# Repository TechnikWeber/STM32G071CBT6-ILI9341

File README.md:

# STM32G071 touch display board (ILI9341)

<p>

</p>

A custom STM32G071CBT6 board that carries an ILI9341 SPI TFT display on its back, with
demo firmware.

## What is on it

| Part | Purpose |
|---|---|
| STM32G071CBT6 | Cortex-M0+ MCU, 128 KB flash, 36 KB RAM |
| 16 MHz and 32.768 kHz crystals | Main clock and RTC |
| AMS1117-3.3 | 5 V → 3.3 V regulator |
| ILI9341 headers | The display module (SPI) |
| Tag-Connect TC2030 footprint (DEBUG) | SWD programming and debugging — see the [STDC14-to-TC2030 adapter](https://github.com/TechnikWeber/STDC14-to-TC2030-IDC) |
| 3-pin headers | UART (RX, TX, GND) and power (5 V, 3.3 V, GND) |
| RESET, BOOT0 and USER buttons, red LED | |

## Files

- `STM32G071.kicad_sch` / `.kicad_pcb` — schematic and PCB (KiCad)
- [`production/`](production) — Gerber/drill zip, BOM, positions and netlist
- [`Firmware/Display.7z`](Firmware) — STM32CubeIDE demo project for the display

## Known issue

> [!WARNING]
> **The ILI9341 footprint does not match** the display module that was bought
> ([AliExpress listing](https://de.aliexpress.com/item/32847628219.html)) — check the
> module's pin spacing and mounting holes before ordering boards.

## Pictures

## License

[MIT](LICENSE).

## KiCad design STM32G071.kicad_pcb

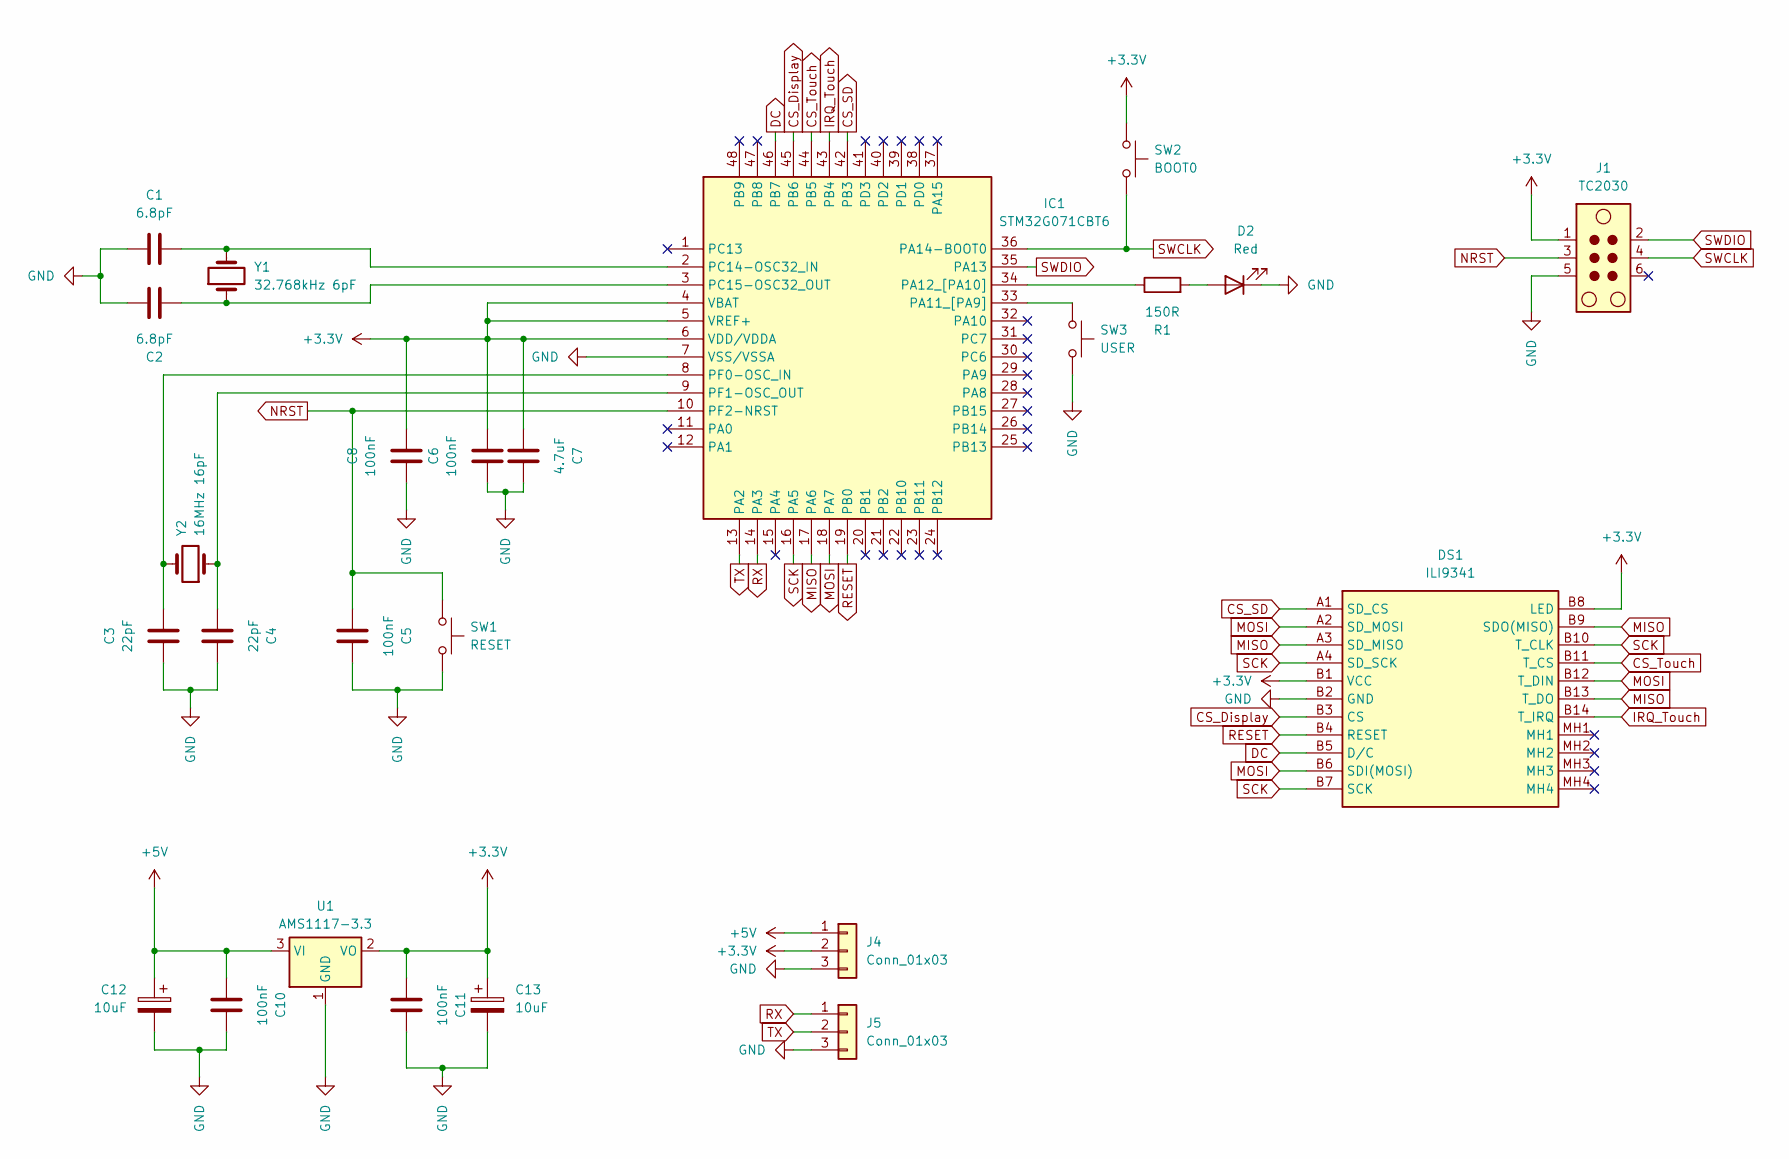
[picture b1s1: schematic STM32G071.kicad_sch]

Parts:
C1, C2: 6.8pF; C_0805_2012Metric; JLC C1832
C3: 22pF; C_0805_2012Metric; JLC C1804
C4: 22pF; C_0805_2012Metric
C5, C6, C8, C10, C11: 100nF; C_0805_2012Metric; JLC C49678
C7: 4.7uF; C_0805_2012Metric; JLC C1779
C12, C13: 10uF; CP_Radial_D6.3mm_P2.50mm
D2: Red; LED_0805_2012Metric
DS1: ILI9341; Manufacturer_Part_Number ILI9341
IC1: STM32G071CBT6; QFP50P900X900X160-48N; Manufacturer_Part_Number STM32G071CBT6; Mouser Part Number 511-STM32G071CBT6
J1: TC2030; Tag-Connect_TC2030-IDC-FP_2x03_P1.27mm_Vertical
J4, J5: Conn_01x03; PinHeader_1x03_P2.54mm_Vertical
R1: 150R; R_0805_2012Metric; JLC C17471
SW1: RESET; SW_SPST_PTS645Sx43SMTR92; JLC C7470157
SW2: BOOT0; SW_SPST_PTS645Sx43SMTR92; JLC C7470157
SW3: USER; SW_SPST_PTS645Sx43SMTR92; JLC C7470157
U1: AMS1117-3.3; SOT-223-3_TabPin2
Y1: 32.768kHz 6pF; Crystal_SMD_3215-2Pin_3.2x1.5mm; JLC C95361
Y2: 16MHz 16pF; Crystal_SMD_HC49-SD; JLC C19631568

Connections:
+3.3V: C6.2, C7.2, C8.2, C11.2, C13.1, DS1.B1 (VCC), DS1.B8 (LED), IC1.4 (VBAT), IC1.5 (VREF+), IC1.6 (VDD/VDDA), J1.1, J4.2, SW2.1, U1.2 (VO)
+5V: C10.2, C12.1, J4.1, U1.3 (VI)
CS_Display: DS1.B3 (CS), IC1.45 (PB6)
CS_SD: DS1.A1 (SD_CS), IC1.42 (PB3)
CS_Touch: DS1.B11 (T_CS), IC1.44 (PB5)
DC: DS1.B5 (D/C), IC1.46 (PB7)
GND: C1.1, C2.1, C3.1, C4.1, C5.1, C6.1, C7.1, C8.1, C10.1, C11.1, C12.2, C13.2, D2.1 (K), DS1.B2 (GND), IC1.7 (VSS/VSSA), J1.5, J4.3, J5.3, SW1.2, SW3.2, U1.1 (GND)
IRQ_Touch: DS1.B14 (T_IRQ), IC1.43 (PB4)
MISO: DS1.A3 (SD_MISO), DS1.B9 (SDO(MISO)), DS1.B13 (T_DO), IC1.17 (PA6)
MOSI: DS1.A2 (SD_MOSI), DS1.B6 (SDI(MOSI)), DS1.B12 (T_DIN), IC1.18 (PA7)
NRST: C5.2, IC1.10 (PF2-NRST), J1.3, SW1.1
unnamed: D2.2 (A), R1.2
unnamed: IC1.33 (PA11_[PA9]), SW3.1
unnamed: IC1.34 (PA12_[PA10]), R1.1
unnamed: C1.2, IC1.2 (PC14-OSC32_IN), Y1.2
unnamed: C2.2, IC1.3 (PC15-OSC32_OUT), Y1.1
unnamed: C3.2, IC1.8 (PF0-OSC_IN), Y2.2
unnamed: C4.2, IC1.9 (PF1-OSC_OUT), Y2.1
RESET: DS1.B4 (RESET), IC1.19 (PB0)
RX: IC1.14 (PA3), J5.1
SCK: DS1.A4 (SD_SCK), DS1.B7 (SCK), DS1.B10 (T_CLK), IC1.16 (PA5)
SWCLK: IC1.36 (PA14-BOOT0), J1.4, SW2.2
SWDIO: IC1.35 (PA13), J1.2
TX: IC1.13 (PA2), J5.2

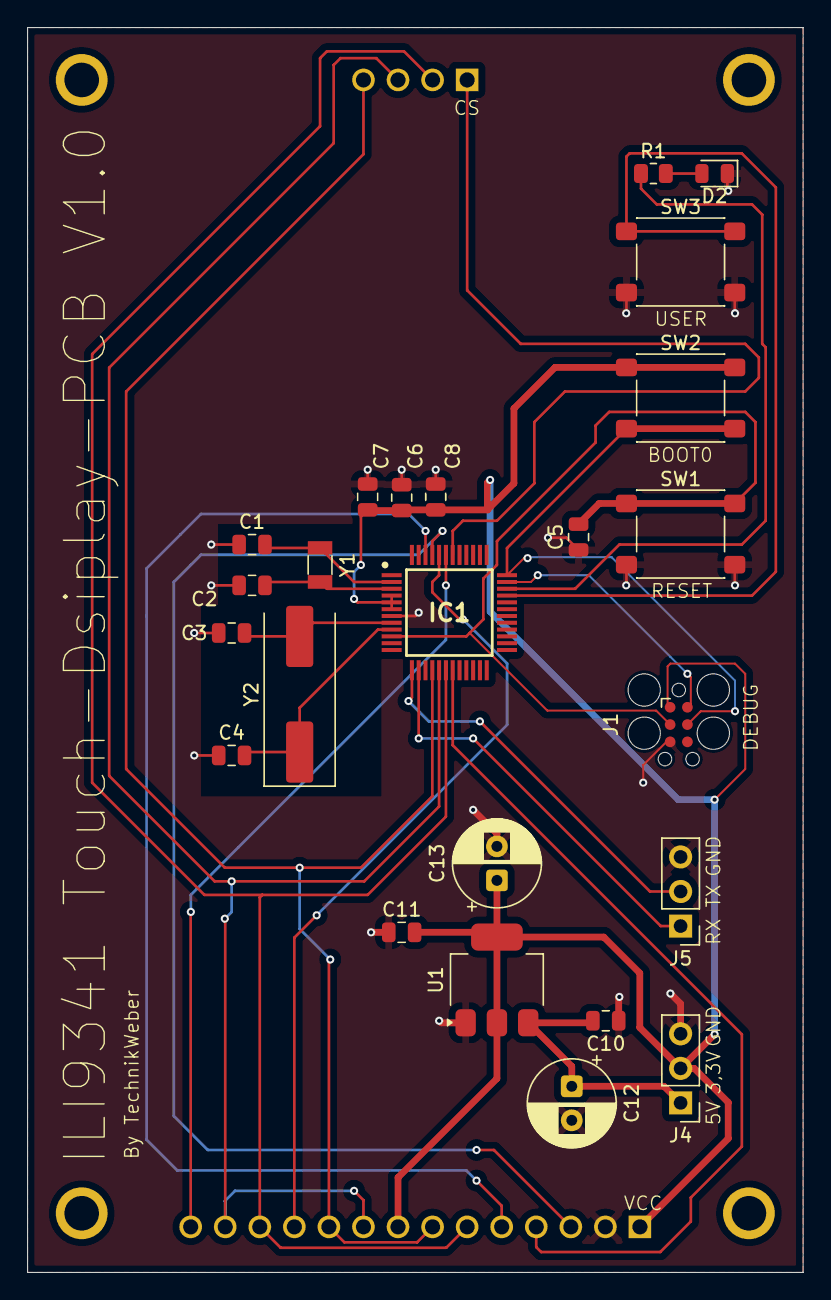
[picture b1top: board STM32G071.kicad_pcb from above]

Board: 2 copper layers, 57.0 x 91.5 mm, 25 parts (1 on the bottom side), 24 nets.

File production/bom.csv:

Designator,Footprint,Quantity,Value,LCSC Part #
"C1, C2",0805,2,6.8pF,
"C10, C11, C5, C6, C8",0805,5,100nF,
"C12, C13",CP_Radial_D6.3mm_P2.50mm,2,10uF,
"C3, C4",0805,2,22pF,
C7,0805,1,4.7uF,
D2,0805,1,Red,
DS1,ILI9341,1,ILI9341,
IC1,QFP50P900X900X160-48N,1,STM32G071CBT6,C432212
"J4, J5",PinHeader_1x03_P2.54mm_Vertical,2,Conn_01x03,
R1,0805,1,150R,
SW1,SW_SPST_PTS645Sx43SMTR92,1,RESET,C7470157
SW2,SW_SPST_PTS645Sx43SMTR92,1,BOOT0,C7470157
SW3,SW_SPST_PTS645Sx43SMTR92,1,USER,C7470157
U1,SOT-223-3_TabPin2,1,AMS1117-3.3,
Y1,Crystal_SMD_3215-2Pin_3.2x1.5mm,1,32.768kHz 6pF,C95361
Y2,Crystal_SMD_HC49-SD,1,16MHz 16pF,C19631568

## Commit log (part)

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2026-03-19 Add image to README
2026-04-10 Update README with images and known issues
    Added images and known problems section to README.
2026-04-10 Fix image tags and update 'Known problems' to 'Known issues'
    Updated image syntax and corrected section title.
2026-04-10 Add files via upload
    Display, touch, led and button is working.
2026-04-10 Added demo firmware
